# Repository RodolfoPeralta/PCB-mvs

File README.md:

# PCB mvs
 Diseño en Eagle de la placa para el sistema MVS (medidor subacuático de la velocidad del sonido).

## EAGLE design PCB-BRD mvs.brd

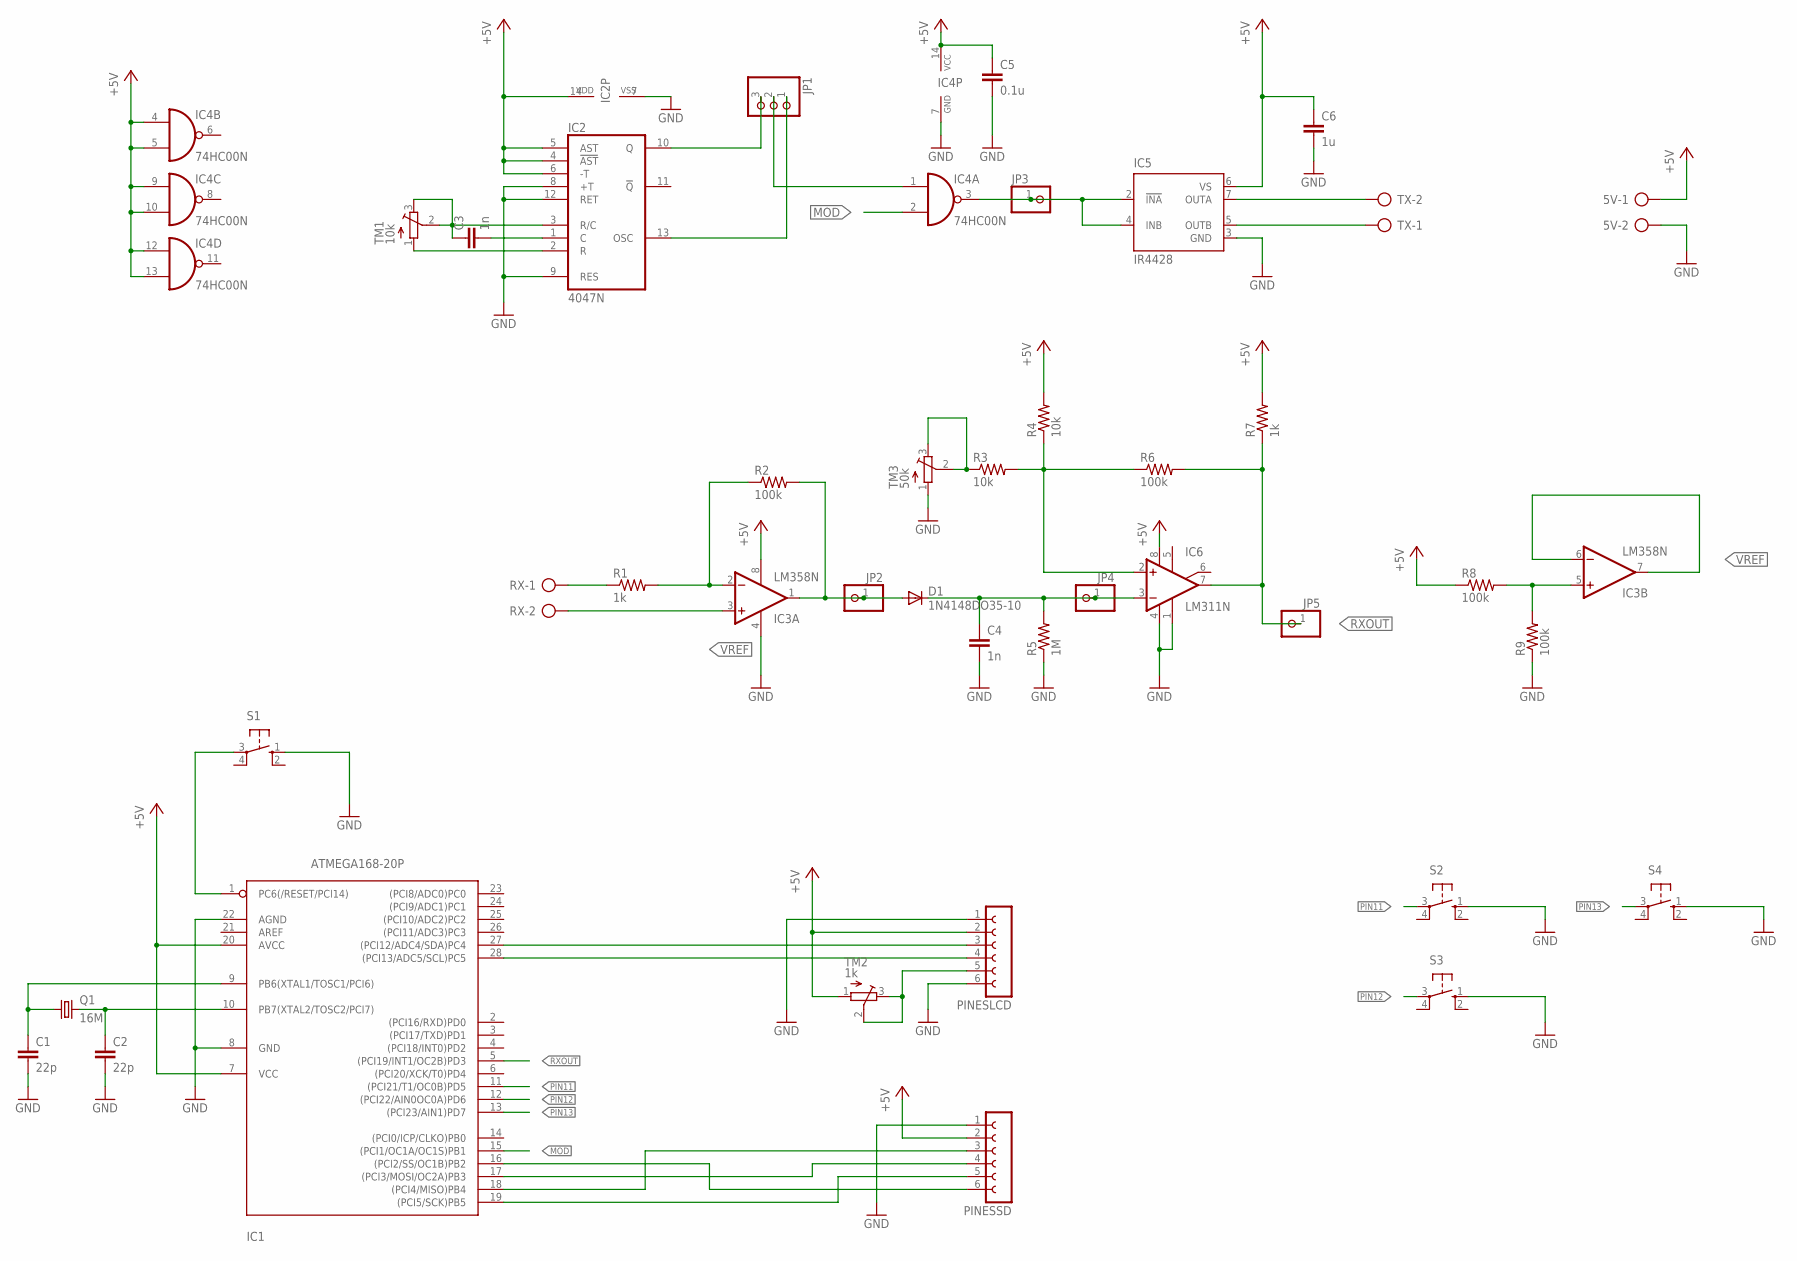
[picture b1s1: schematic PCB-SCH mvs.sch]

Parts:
5V: AK500/2
C1, C2: 22p; C050-024X044
C3, C4: 1n; C050-024X044
C5: 0.1u; C050-024X044
C6: 1u; C050-024X044
D1: 1N4148DO35-10; DO35-10
IC1: ATMEGA168-20P; DIL28-3
IC2: 4047N; DIL14
IC3: LM358N; DIL08
IC4: 74HC00N; DIL14
IC5: IR4428; DIL08
IC6: LM311N; DIL08
JP1: PINHD-1X3; 1X03
JP2, JP3, JP4, JP5: PINHD-1X1; 1X01
PINESLCD: FE06-1; FE06
PINESSD: FE06-1; FE06
Q1: 16M; HC49U-V
R1, R7: 1k; 0207/10
R2, R6, R8, R9: 100k; 0207/10
R3, R4: 10k; 0207/10
R5: 1M; 0207/10
RX: AK500/2
S1, S2, S3, S4: 10-XX; B3F-10XX
TM1: 10k; TRIM-3386
TM2: 1k; TRIM-3386
TM3: 50k; TRIM-3386
TX: AK500/2

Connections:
+5V: 5V.1, C5.1, C6.1, IC1.7 (VCC), IC1.20 (AVCC), IC2.4 (!AST), IC2.5 (AST), IC2.6 (-T), IC2.14 (VDD), IC3.8 (V+), IC4.4 (I0), IC4.5 (I1), IC4.9 (I0), IC4.10 (I1), IC4.12 (I0), IC4.13 (I1), IC4.14 (VCC), IC5.6 (VS), IC6.8 (V+), PINESLCD.2, PINESSD.2, R4.2, R7.2, R8.1, TM2.1 (A)
GND: 5V.2, C1.2, C2.2, C4.2, C5.2, C6.2, IC1.8 (GND), IC1.22 (AGND), IC2.7 (VSS), IC2.8 (+T), IC2.9 (RES), IC2.12 (RET), IC3.4 (V-), IC4.7 (GND), IC5.3 (GND), IC6.1 (GND), IC6.4 (V-), PINESLCD.1, PINESLCD.6, PINESSD.1, R5.1, R9.1, S1.1 (S), S2.1 (S), S3.1 (S), S4.1 (S), TM3.1 (A)
MOD: IC1.15 ((PCI1/OC1A/OC1S)PB1), IC4.2 (I1)
unnamed: IC2.10 (Q), JP1.3
unnamed: IC2.13 (OSC), JP1.1
unnamed: IC4.1 (I0), JP1.2
unnamed: IC2.2 (R), TM1.1 (A)
unnamed: IC5.7 (OUTA), TX.2
unnamed: IC5.5 (OUTB), TX.1
unnamed: R1.1, RX.1
unnamed: IC3.2 (-IN), R1.2, R2.1
unnamed: C1.1, IC1.9 (PB6(XTAL1/TOSC1/PCI6)), Q1.1
unnamed: IC6.2 (+IN), R3.2, R4.1, R6.1
unnamed: C3.2, IC2.1 (C)
unnamed: R3.1, TM3.2 (S), TM3.3 (E)
unnamed: C3.1, IC2.3 (R/C), TM1.2 (S), TM1.3 (E)
unnamed: C2.1, IC1.10 (PB7(XTAL2/TOSC2/PCI7)), Q1.2
unnamed: IC4.3 (O), IC5.2 (!INA), IC5.4 (INB), JP3.1
unnamed: D1.A, IC3.1 (OUT), JP2.1, R2.2
unnamed: IC3.5 (+IN), R8.2, R9.2
unnamed: IC1.17 ((PCI3/MOSI/OC2A)PB3), PINESSD.4
unnamed: IC1.18 ((PCI4/MISO)PB4), PINESSD.3
unnamed: IC1.1 (PC6(/RESET/PCI14)), S1.3
unnamed: C4.1, D1.C, IC6.3 (-IN), JP4.1, R5.2
unnamed: IC1.19 ((PCI5/SCK)PB5), PINESSD.5
unnamed: IC1.16 ((PCI2/SS/OC1B)PB2), PINESSD.6
unnamed: IC1.27 ((PCI12/ADC4/SDA)PC4), PINESLCD.3
unnamed: IC1.28 ((PCI13/ADC5/SCL)PC5), PINESLCD.4
unnamed: PINESLCD.5, TM2.2 (S), TM2.3 (E)
PIN11: IC1.11 ((PCI21/T1/OC0B)PD5), S2.3
PIN12: IC1.12 ((PCI22/AIN0OC0A)PD6), S3.3
PIN13: IC1.13 ((PCI23/AIN1)PD7), S4.3
RXOUT: IC1.5 ((PCI19/INT1/OC2B)PD3), IC6.7 (OUT), JP5.1, R6.2, R7.1
VREF: IC3.3 (+IN), IC3.6 (-IN), IC3.7 (OUT), RX.2

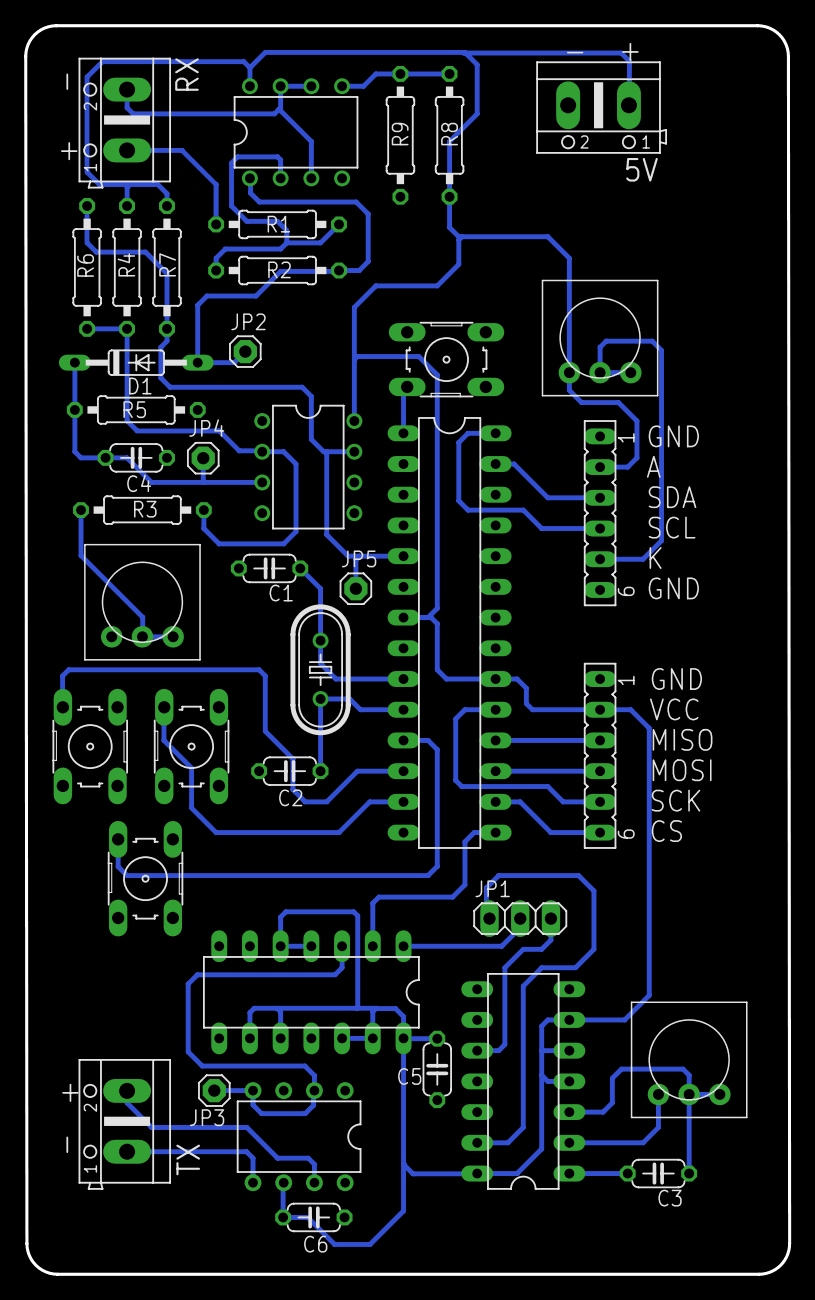
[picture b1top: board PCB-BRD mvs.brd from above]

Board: 2 copper layers, 63.2 x 103.3 mm, 40 parts (0 on the bottom side), 34 nets.

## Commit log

2022-05-10 SCH-BRD
2022-05-12 imágenes
